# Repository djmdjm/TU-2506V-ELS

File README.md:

# Electronic Leadscrew for Optimum TU-2506V

This is a project to build an Electronic Leadscrew (ELS) for my bench
lathe, an Optimum TU-2506V. There are other lathes on the market that
seem to be based on the same casting (e.g. the Weiss WBL250F) that
might be compatible.

The project contains CAD designs for the mechanical parts, schematics,
PCB designs and firmware for the control board. More build photos
[here](https://photos.google.com/share/AF1QipOmF3oVsJtj0tLDA7D8ZUFRA7_QTG3Cf1XSVP2GjohUuVMBAQHxomHKcaGD1ETOJg?key=TW1sOVEwWHhqX3FoNWtXSDA4Q3BxZG1Bc1JGLTBn).

## Caveat

This works fine for me, but I'm just some guy on the internet with
little or no mechanical, electronic or software engineering training. 
There is no warranty for any of this, no guarantee that it will work,
no guarantee that it won't destroy your lathe, no promise that the
software won't crash in the middle of a job and scrap your part, etc.

Many of the mechanical pieces were manually made and even the
ones I CNC'd or had fabricated received some modifications that
aren't reflected in the CAD files. If you want to use this as the
basis of your own ELS, then be prepared to do some modifications of
your own.

## What you'll need (software)

The mechanical CAD designs were done in
[FreeCAD](https://www.freecad.org/) 0.21. For the parts that I CNC'd
myself, I also used FreeCAD's CAM processor to generate the G-Code.

The control boards was designed in [KiCAD](https://www.kicad.org/)
version 8 and were fabricated at JLCPCB. The PCB files have LCSC
annotations for automated assembly of the (few) SMT components.

The firmware for the control board was written in Rust using the
[stm32f4xx_hal](https://github.com/stm32-rs/stm32f4xx-hal) package.
I used rustc 1.81.0, but other versions might work too.

## What you'll need (hardware)

This lists only the main components. There are many small parts that
should be obvious from the CAD files, not to mention custom parts that
you'll need to make yourself or have fabricated.

The controller was designed around a
[STM32F411 "black pill"](https://www.dfrobot.com/product-2338.html) board.
These are also easily and cheaply available from hobbyist electronics
suppliers and from Ebay/Aliexpress.

The display is a
[Newhaven M0216SD‐162SDAR2-1](https://au.mouser.com/ProductDetail/Newhaven-Display/M0216SD-162SDAR2-1?qs=3vk7fz9CmNxwBN2LYkSmDA%3D%3D)
vacuum fluorescent display that I ordered from Mouser - this is a
fairly expensive part, but I love the aesthetics of a VFD.

The rest of the BOM for the controller can be extracted from the
KiCAD files for each of the respective boards. I mostly used parts that
I had on hand, so there are some odd choices in places.

The controller needs a 24VDC power supply at about 250mA in addition to
whatever the servo control needs. I used a Meanwell DIN rail mount PSU.

The servo motor I used a
[Teknic Clearpath CPM-SDSK-2331S-ELS](https://teknic.com/model-info/CPM-SDSK-2331S-ELS/).
Again, this is a fairly expensive choice and a cheaper stepper
motor + controller would probably do fine. The Clearpath drive does
have some very nice advantages over plain steppers or even cheap
closed-loop stepper drives. Whatever drive you choose, it obviously
needs to fit (NEMA 23 was close to the limit on my lathe) and you'll
need to provide a suitable power supply for it.

The spindle encoder I used was an
[Omron E6B2-CWZ1X](https://www.ia.omron.com/product/item/2382/). These are
ridiculously expensive if you buy them from anywhere reputable, but very
cheap on Ebay or Aliexpress.

The timing pulleys and belt used to connect the servo to the
leadscrew are standard HTD 5M parts. I got mine from PT Parts
([pulleys](https://www.ptparts.com.au/products/category/ALL/-12-5M-15--5m-15-htd-timing-pulleys):
20-5M-15F 40-5M-15F,
[belt](https://www.ptparts.com.au/products/category/ALL/-225-5M-15--5m-15-timing-belts): 350-5M-15),
but they should be fairly standard.

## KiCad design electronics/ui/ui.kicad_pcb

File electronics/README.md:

# Controller schematics and PCB designs

This directory contains the schematics and PCB CAD files for the controller
boards. To fit in the available space in the lathe casting they are designed
as a stack.

The `mcu/` subdirectory contains the designs for the MCU carrier board, which
basically exists to route signals from the STM32F411 Black Pill board to the
adjacent ones via headers. The character VFD display also connects to this
board via extended headers.

The `pwr_io/` subdirectory has the design for the isolated power and I/O board.
It has a couple of modular DC-DC converters that provide an isolated supply
to the MCU and display, and a separate isolated supply for the spindle encoder
and servo control lines.

The `ui/` subdirectory has the design for the carrier board for the rotary
encoders used on the front panel (you'll need two of these). These connect
via cables terminated in IDC connectors on the MCU board.

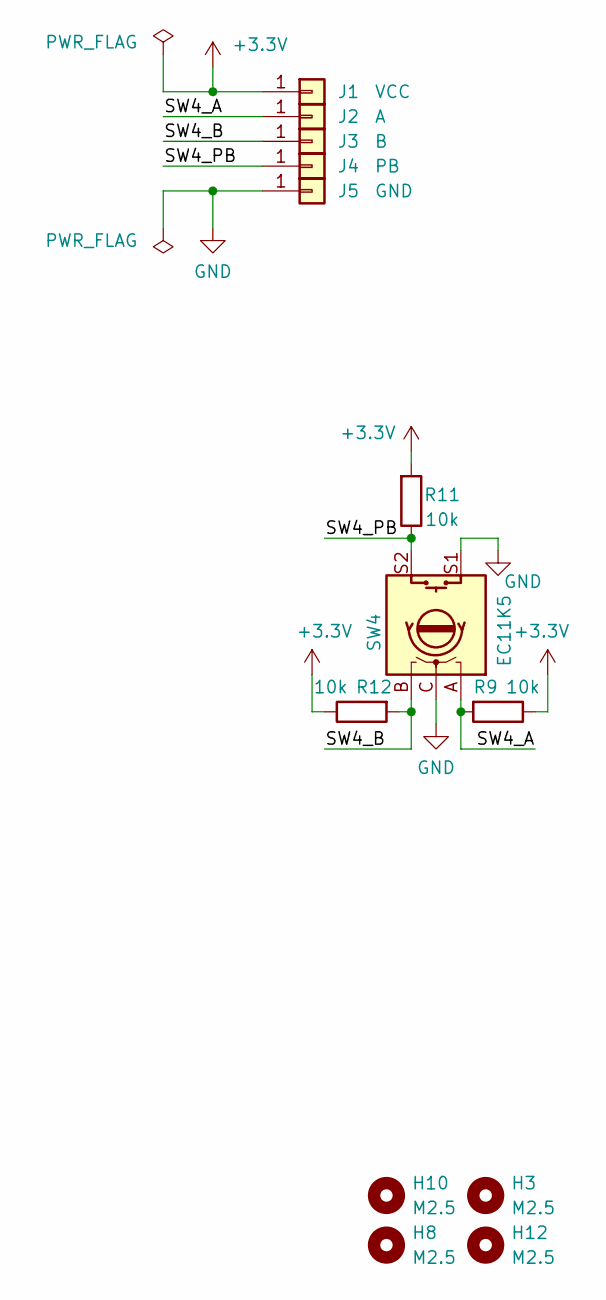
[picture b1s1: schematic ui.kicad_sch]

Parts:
H3, H8, H10, H12: M2.5; MountingHole_2.2mm_M2
J1: VCC; TestPoint_THTPad_D1.0mm_Drill0.5mm
J2: A; TestPoint_THTPad_D1.0mm_Drill0.5mm
J3: B; TestPoint_THTPad_D1.0mm_Drill0.5mm
J4: PB; TestPoint_THTPad_D1.0mm_Drill0.5mm
J5: GND; TestPoint_THTPad_D1.0mm_Drill0.5mm
R9, R11, R12: 10k; R_0805_2012Metric; LCSC C17414
SW4: EC11K5; EC11K15

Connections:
+3.3V: J1.1, R9.1, R11.2, R12.1
/SW4_A: J2.1, R9.2, SW4.A
/SW4_B: J3.1, R12.2, SW4.B
/SW4_PB: J4.1, R11.1, SW4.S2
GND: J5.1, SW4.C, SW4.S1

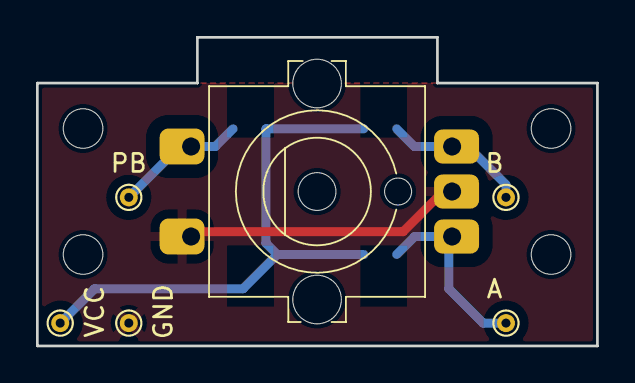
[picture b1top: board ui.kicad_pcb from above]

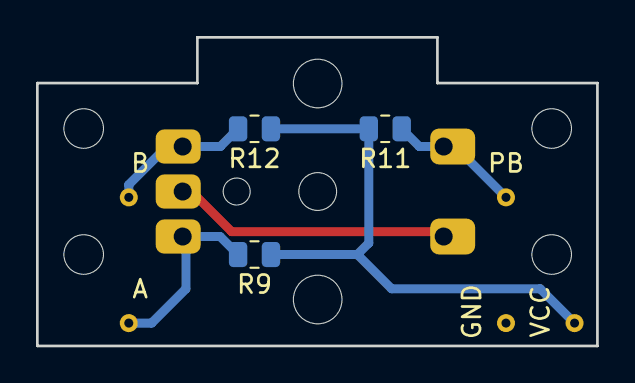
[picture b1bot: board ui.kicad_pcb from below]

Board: 2 copper layers, 31.1 x 17.1 mm, 13 parts (3 on the bottom side), 5 nets.

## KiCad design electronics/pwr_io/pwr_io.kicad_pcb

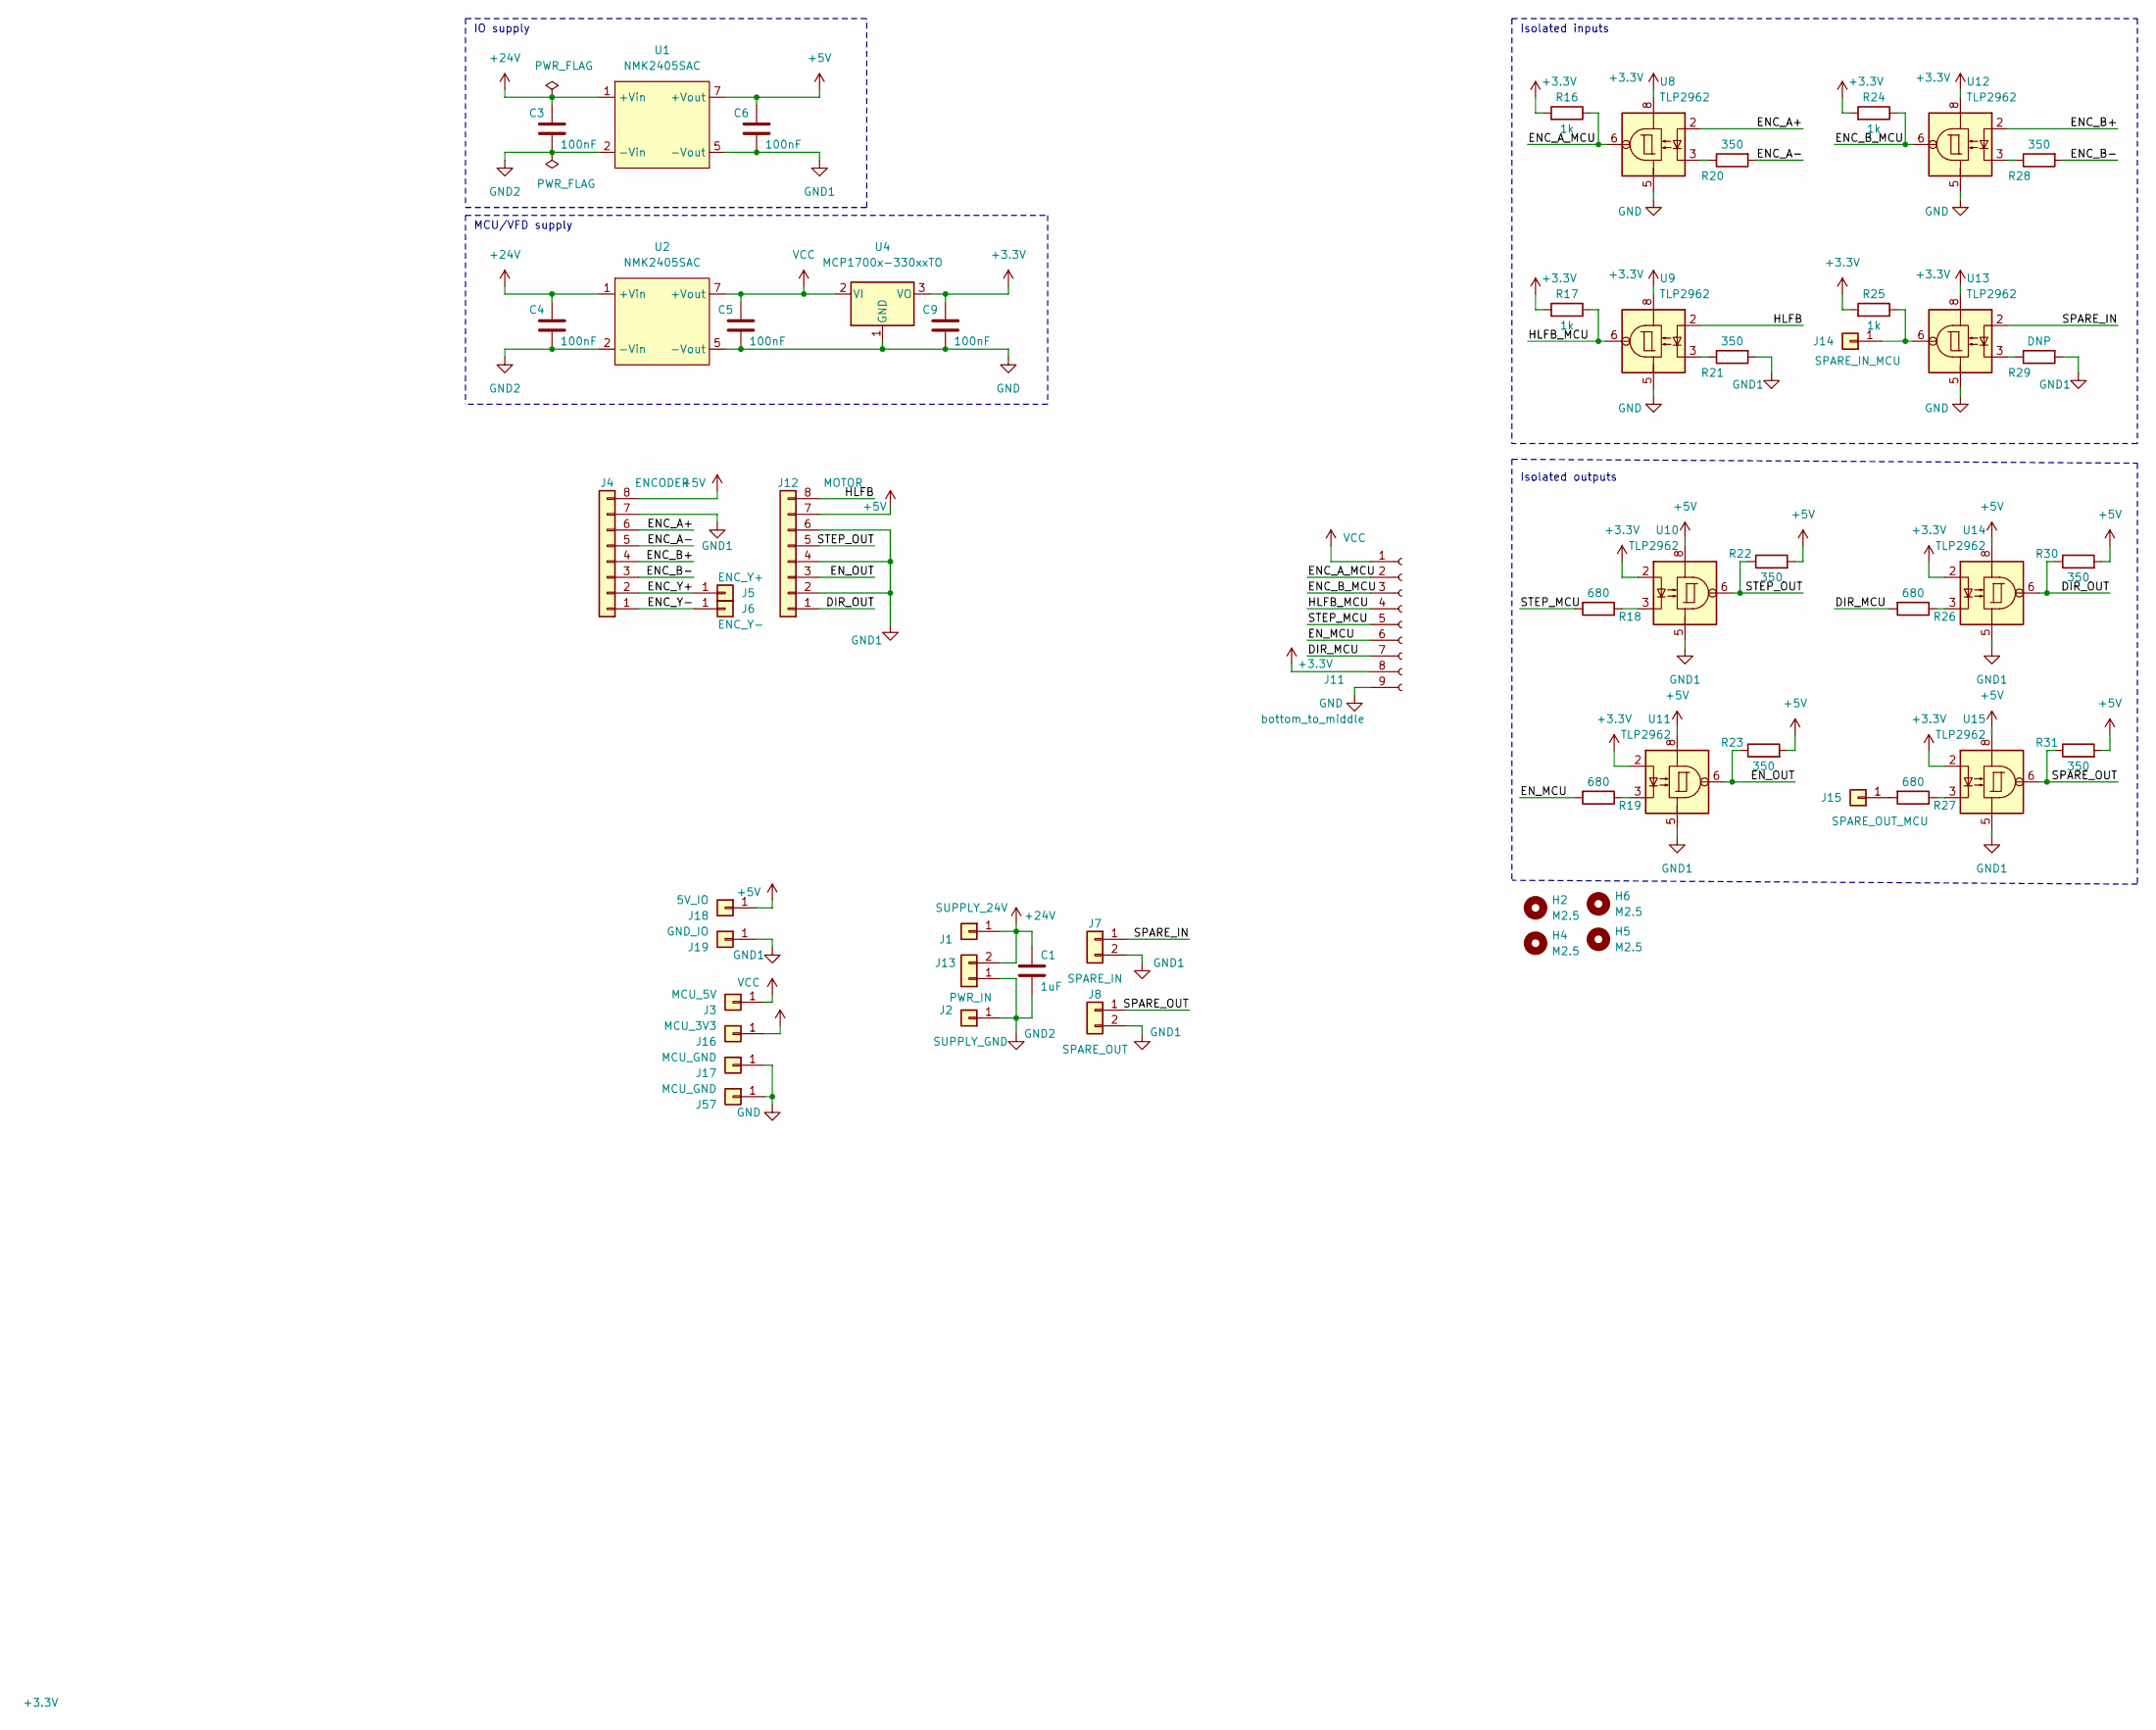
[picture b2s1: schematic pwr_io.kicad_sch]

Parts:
C1: 1uF; C_0805_2012Metric; LCSC C28323
C3, C4, C5, C6, C9: 100nF; C_0805_2012Metric; LCSC C28233
H2, H4, H5, H6: M2.5; MountingHole_2.7mm_M2.5
J1: SUPPLY_24V; TestPoint_THTPad_D1.5mm_Drill0.7mm
J2: SUPPLY_GND; TestPoint_THTPad_D1.5mm_Drill0.7mm
J3: MCU_5V; TestPoint_THTPad_D1.5mm_Drill0.7mm
J4: ENCODER; TerminalBlock_Phoenix_MKDS-1,5-8_1x08_P5.00mm_Horizontal
J5: ENC_Y+; TestPoint_THTPad_D1.5mm_Drill0.7mm
J6: ENC_Y-; TestPoint_THTPad_D1.5mm_Drill0.7mm
J7: SPARE_IN; TerminalBlock_Phoenix_MKDS-1,5-2_1x02_P5.00mm_Horizontal
J8: SPARE_OUT; TerminalBlock_Phoenix_MKDS-1,5-2_1x02_P5.00mm_Horizontal
J11: bottom_to_middle; PinHeader_1x09_P2.54mm_Vertical
J12: MOTOR; TerminalBlock_Phoenix_MKDS-1,5-8_1x08_P5.00mm_Horizontal
J13: PWR_IN; TerminalBlock_Phoenix_MKDS-1,5-2_1x02_P5.00mm_Horizontal
J14: SPARE_IN_MCU; TestPoint_THTPad_D1.5mm_Drill0.7mm
J15: SPARE_OUT_MCU; TestPoint_THTPad_D1.5mm_Drill0.7mm
J16: MCU_3V3; TestPoint_THTPad_D1.5mm_Drill0.7mm
J17, J57: MCU_GND; TestPoint_THTPad_D1.5mm_Drill0.7mm
J18: 5V_IO; TestPoint_THTPad_D1.5mm_Drill0.7mm
J19: GND_IO; TestPoint_THTPad_D1.5mm_Drill0.7mm
R16, R17, R24, R25: 1k; R_0805_2012Metric; LCSC C17513
R18, R19, R26, R27: 680; R_0805_2012Metric; LCSC C93658
R20, R21, R22, R23, R28, R30, R31: 350; R_0805_2012Metric; LCSC C245312
R29: DNP; R_0805_2012Metric
U1, U2: NMK2405SAC; NMK_single_output
U4: MCP1700x-330xxTO; TO-92_Inline
U8, U9, U10, U11, U12, U13, U14, U15: TLP2962; DIP-8_W7.62mm

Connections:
+3.3V: C9.1, J11.8, J16.1, R16.2, R17.2, R24.2, R25.2, U4.3 (VO), U8.8, U9.8, U10.2, U11.2, U12.8, U13.8, U14.2, U15.2
+5V: C6.1, J4.8, J12.7, J18.1, R22.2, R23.2, R30.2, R31.2, U1.7 (+Vout), U10.8, U11.8, U14.8, U15.8
+24V: C1.1, C3.1, C4.1, J1.1, J13.2, U1.1 (+Vin), U2.1 (+Vin)
/DIR_MCU: J11.7, R26.2
/DIR_OUT: J12.1, R30.1, U14.6
/ENC_A+: J4.6, U8.2
/ENC_A-: J4.5, R20.2
/ENC_A_MCU: J11.2, R16.1, U8.6
/ENC_B+: J4.4, U12.2
/ENC_B-: J4.3, R28.2
/ENC_B_MCU: J11.3, R24.1, U12.6
/ENC_Y+: J4.2, J5.1
/ENC_Y-: J4.1, J6.1
/EN_MCU: J11.6, R19.2
/EN_OUT: J12.3, R23.1, U11.6
/HLFB: J12.8, U9.2
/HLFB_MCU: J11.4, R17.1, U9.6
/SPARE_IN: J7.1, U13.2
/SPARE_OUT: J8.1, R31.1, U15.6
/STEP_MCU: J11.5, R18.2
/STEP_OUT: J12.5, R22.1, U10.6
GND: C5.2, C9.2, J11.9, J17.1, J57.1, U2.5 (-Vout), U4.1 (GND), U8.5, U9.5, U12.5, U13.5
GND1: C6.2, J4.7, J7.2, J8.2, J12.2, J12.4, J12.6, J19.1, R21.2, R29.2, U1.5 (-Vout), U10.5, U11.5, U14.5, U15.5
GND2: C1.2, C3.2, C4.2, J2.1, J13.1, U1.2 (-Vin), U2.2 (-Vin)
unnamed: J14.1, R25.1, U13.6
unnamed: J15.1, R27.2
unnamed: R18.1, U10.3
unnamed: R19.1, U11.3
unnamed: R20.1, U8.3
unnamed: R21.1, U9.3
unnamed: R26.1, U14.3
unnamed: R27.1, U15.3
unnamed: R28.1, U12.3
unnamed: R29.1, U13.3
VCC: C5.1, J3.1, J11.1, U2.7 (+Vout), U4.2 (VI)

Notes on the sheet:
Isolated outputs
Isolated inputs
IO supply
MCU/VFD supply

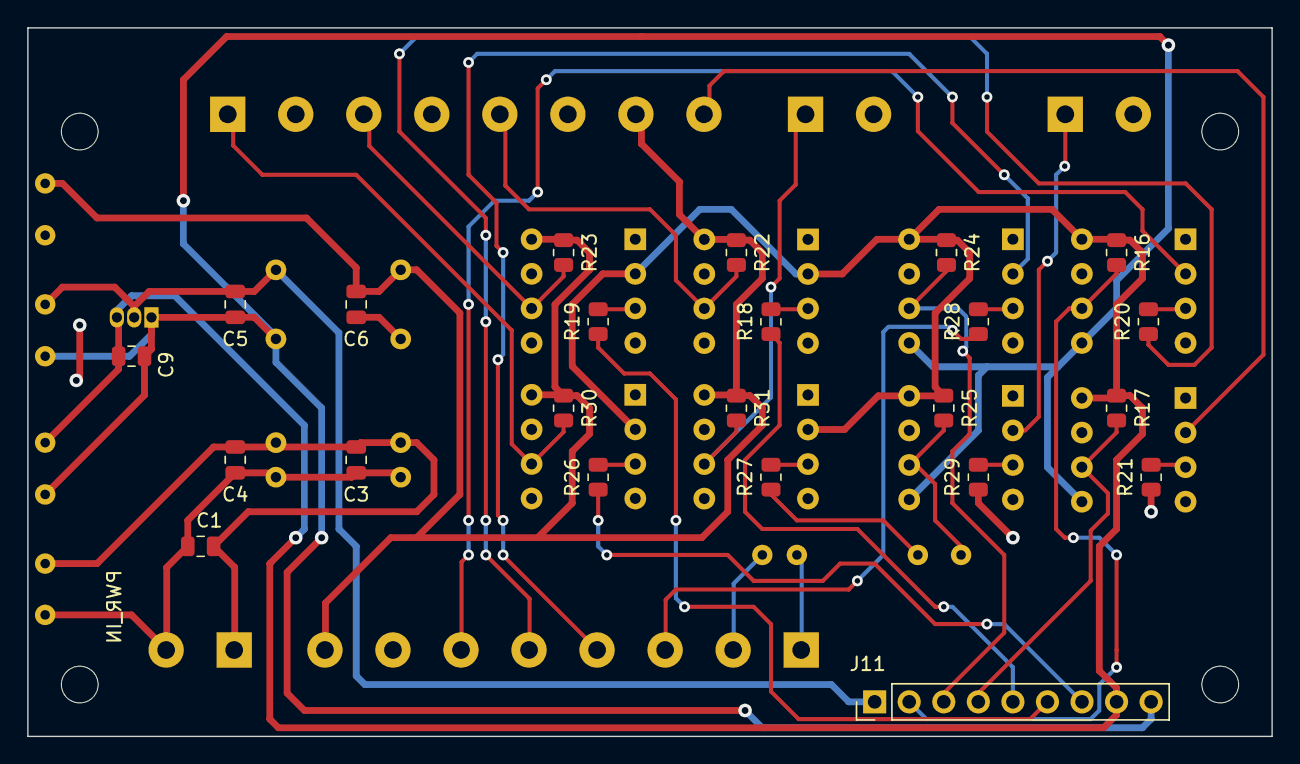
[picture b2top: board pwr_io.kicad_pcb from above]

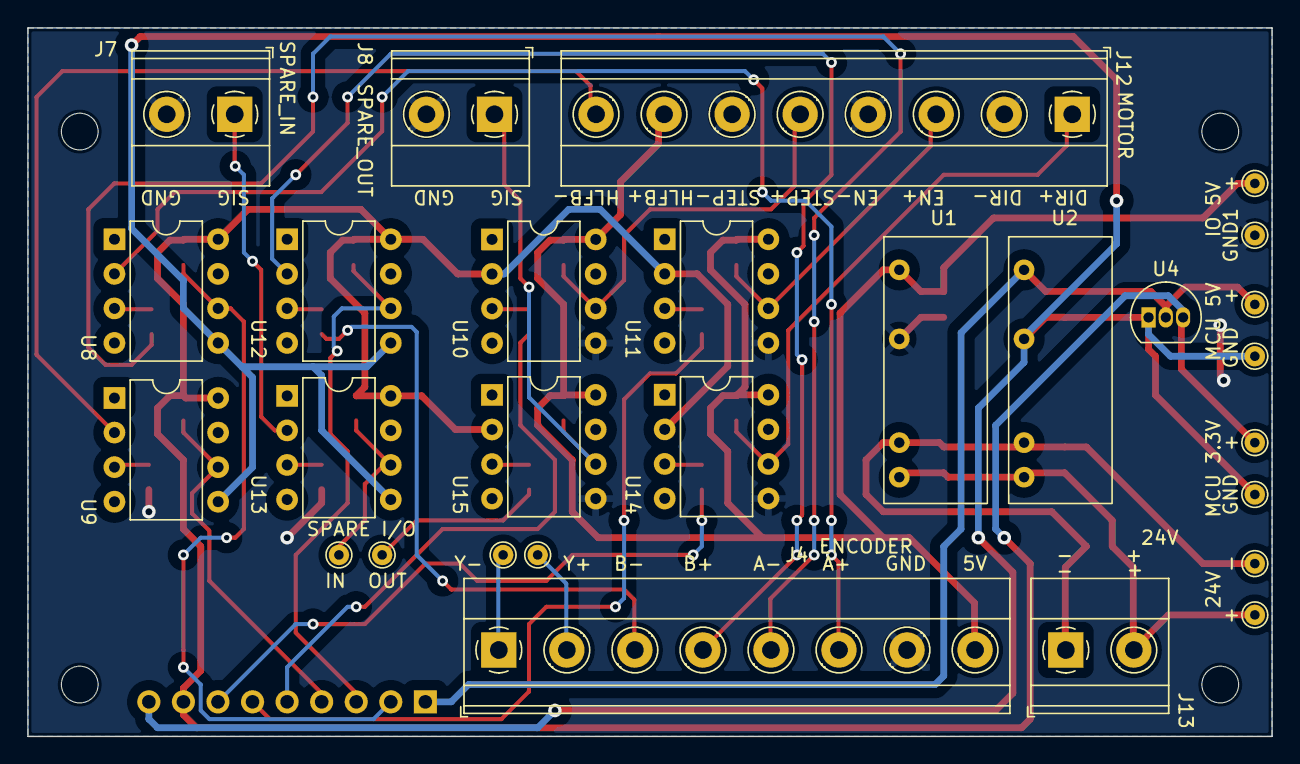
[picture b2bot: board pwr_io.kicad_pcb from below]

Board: 2 copper layers, 91.4 x 52.1 mm, 55 parts (28 on the bottom side), 35 nets.

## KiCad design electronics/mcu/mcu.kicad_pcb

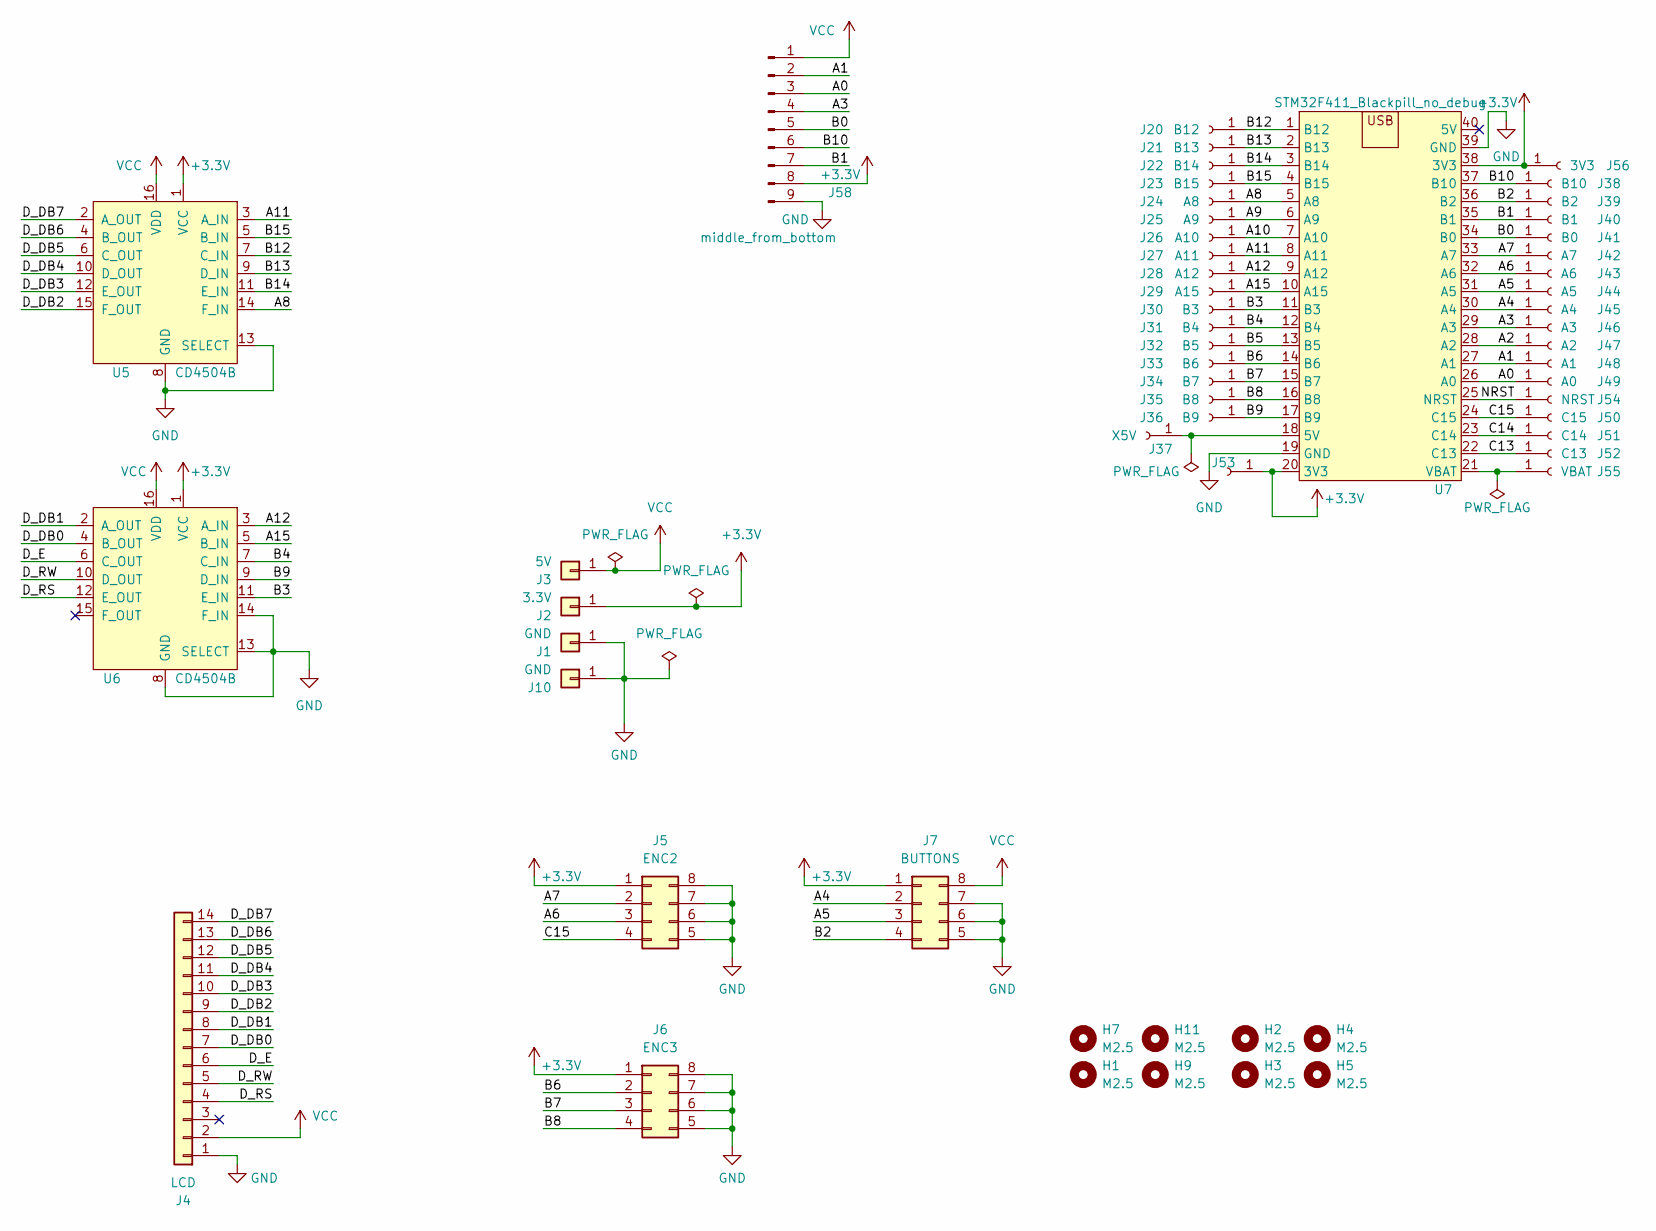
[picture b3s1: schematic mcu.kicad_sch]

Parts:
H1, H2, H3, H4, H5, H7, H9, H11: M2.5; MountingHole_2.7mm_M2.5
J1, J10: GND; TestPoint_THTPad_D1.5mm_Drill0.7mm
J2: 3.3V; TestPoint_THTPad_D1.5mm_Drill0.7mm
J3: 5V; TestPoint_THTPad_D1.5mm_Drill0.7mm
J4: LCD; PinHeader_1x14_P2.54mm_Vertical
J5: ENC2; IDC-Header_2x04_P2.54mm_Vertical
J6: ENC3; IDC-Header_2x04_P2.54mm_Vertical
J7: BUTTONS; IDC-Header_2x04_P2.54mm_Vertical
J20: B12; TestPoint_THTPad_D1.5mm_Drill0.7mm
J21: B13; TestPoint_THTPad_D1.5mm_Drill0.7mm
J22: B14; TestPoint_THTPad_D1.5mm_Drill0.7mm
J23: B15; TestPoint_THTPad_D1.5mm_Drill0.7mm
J24: A8; TestPoint_THTPad_D1.5mm_Drill0.7mm
J25: A9; TestPoint_THTPad_D1.5mm_Drill0.7mm
J26: A10; TestPoint_THTPad_D1.5mm_Drill0.7mm
J27: A11; TestPoint_THTPad_D1.5mm_Drill0.7mm
J28: A12; TestPoint_THTPad_D1.5mm_Drill0.7mm
J29: A15; TestPoint_THTPad_D1.5mm_Drill0.7mm
J30: B3; TestPoint_THTPad_D1.5mm_Drill0.7mm
J31: B4; TestPoint_THTPad_D1.5mm_Drill0.7mm
J32: B5; TestPoint_THTPad_D1.5mm_Drill0.7mm
J33: B6; TestPoint_THTPad_D1.5mm_Drill0.7mm
J34: B7; TestPoint_THTPad_D1.5mm_Drill0.7mm
J35: B8; TestPoint_THTPad_D1.5mm_Drill0.7mm
J36: B9; TestPoint_THTPad_D1.5mm_Drill0.7mm
J37: X5V; TestPoint_THTPad_D1.5mm_Drill0.7mm
J38: B10; TestPoint_THTPad_D1.5mm_Drill0.7mm
J39: B2; TestPoint_THTPad_D1.5mm_Drill0.7mm
J40: B1; TestPoint_THTPad_D1.5mm_Drill0.7mm
J41: B0; TestPoint_THTPad_D1.5mm_Drill0.7mm
J42: A7; TestPoint_THTPad_D1.5mm_Drill0.7mm
J43: A6; TestPoint_THTPad_D1.5mm_Drill0.7mm
J44: A5; TestPoint_THTPad_D1.5mm_Drill0.7mm
J45: A4; TestPoint_THTPad_D1.5mm_Drill0.7mm
J46: A3; TestPoint_THTPad_D1.5mm_Drill0.7mm
J47: A2; TestPoint_THTPad_D1.5mm_Drill0.7mm
J48: A1; TestPoint_THTPad_D1.5mm_Drill0.7mm
J49: A0; TestPoint_THTPad_D1.5mm_Drill0.7mm
J50: C15; TestPoint_THTPad_D1.5mm_Drill0.7mm
J51: C14; TestPoint_THTPad_D1.5mm_Drill0.7mm
J52: C13; TestPoint_THTPad_D1.5mm_Drill0.7mm
J53, J56: 3V3; TestPoint_THTPad_D1.5mm_Drill0.7mm
J54: NRST; TestPoint_THTPad_D1.5mm_Drill0.7mm
J55: VBAT; TestPoint_THTPad_D1.5mm_Drill0.7mm
J58: middle_from_bottom; PinSocket_1x09_P2.54mm_Vertical
U5, U6: CD4504B; DIP-16_W7.62mm
U7: STM32F411_Blackpill_no_debug; BlackPill_V3_no_debug

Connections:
+3.3V: J2.1, J5.1, J6.1, J7.1, J53.1, J56.1, J58.8, U5.1 (VCC), U6.1 (VCC), U7.20 (3V3), U7.38 (3V3)
/A0: J49.1, J58.3, U7.26 (A0)
/A1: J48.1, J58.2, U7.27 (A1)
/A2: J47.1, U7.28 (A2)
/A3: J46.1, J58.4, U7.29 (A3)
/A4: J7.2, J45.1, U7.30 (A4)
/A5: J7.3, J44.1, U7.31 (A5)
/A6: J5.3, J43.1, U7.32 (A6)
/A7: J5.2, J42.1, U7.33 (A7)
/A8: J24.1, U5.14 (F_IN), U7.5 (A8)
/A9: J25.1, U7.6 (A9)
/A10: J26.1, U7.7 (A10)
/A11: J27.1, U5.3 (A_IN), U7.8 (A11)
/A12: J28.1, U6.3 (A_IN), U7.9 (A12)
/A15: J29.1, U6.5 (B_IN), U7.10 (A15)
/B0: J41.1, J58.5, U7.34 (B0)
/B1: J40.1, J58.7, U7.35 (B1)
/B2: J7.4, J39.1, U7.36 (B2)
/B3: J30.1, U6.11 (E_IN), U7.11 (B3)
/B4: J31.1, U6.7 (C_IN), U7.12 (B4)
/B5: J32.1, U7.13 (B5)
/B6: J6.2, J33.1, U7.14 (B6)
/B7: J6.3, J34.1, U7.15 (B7)
/B8: J6.4, J35.1, U7.16 (B8)
/B9: J36.1, U6.9 (D_IN), U7.17 (B9)
/B10: J38.1, J58.6, U7.37 (B10)
/B12: J20.1, U5.7 (C_IN), U7.1 (B12)
/B13: J21.1, U5.9 (D_IN), U7.2 (B13)
/B14: J22.1, U5.11 (E_IN), U7.3 (B14)
/B15: J23.1, U5.5 (B_IN), U7.4 (B15)
/C13: J52.1, U7.22 (C13)
/C14: J51.1, U7.23 (C14)
/C15: J5.4, J50.1, U7.24 (C15)
/D_DB0: J4.7, U6.4 (B_OUT)
/D_DB1: J4.8, U6.2 (A_OUT)
/D_DB2: J4.9, U5.15 (F_OUT)
/D_DB3: J4.10, U5.12 (E_OUT)
/D_DB4: J4.11, U5.10 (D_OUT)
/D_DB5: J4.12, U5.6 (C_OUT)
/D_DB6: J4.13, U5.4 (B_OUT)
/D_DB7: J4.14, U5.2 (A_OUT)
/D_E: J4.6, U6.6 (C_OUT)
/D_RS: J4.4, U6.12 (E_OUT)
/D_RW: J4.5, U6.10 (D_OUT)
/NRST: J54.1, U7.25 (NRST)
GND: J1.1, J4.1, J5.5, J5.6, J5.7, J5.8, J6.5, J6.6, J6.7, J6.8, J7.5, J7.6, J7.7, J10.1, J58.9, U5.8 (GND), U5.13 (SELECT), U6.8 (GND), U6.13 (SELECT), U6.14 (F_IN), U7.19 (GND), U7.39 (GND)
unnamed: J37.1, U7.18 (5V)
unnamed: J55.1, U7.21 (VBAT)
VCC: J3.1, J4.2, J7.8, J58.1, U5.16 (VDD), U6.16 (VDD)

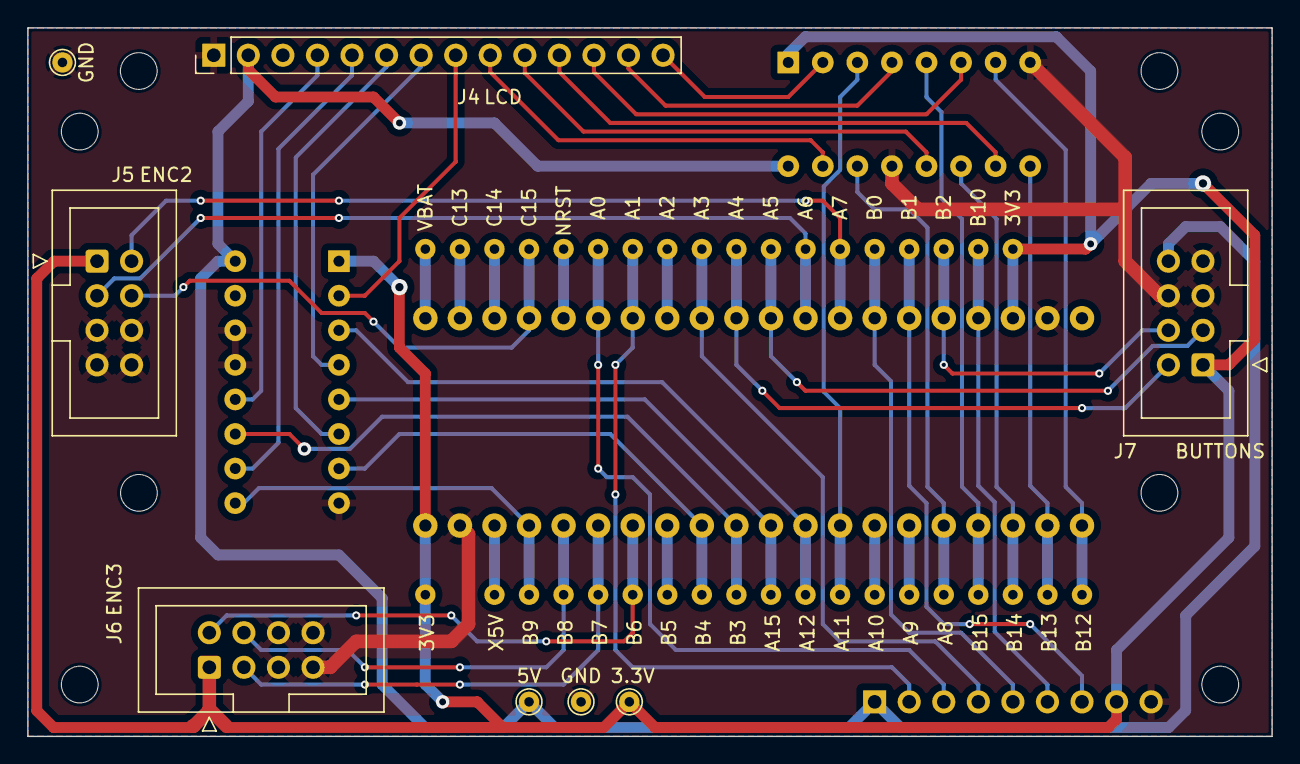
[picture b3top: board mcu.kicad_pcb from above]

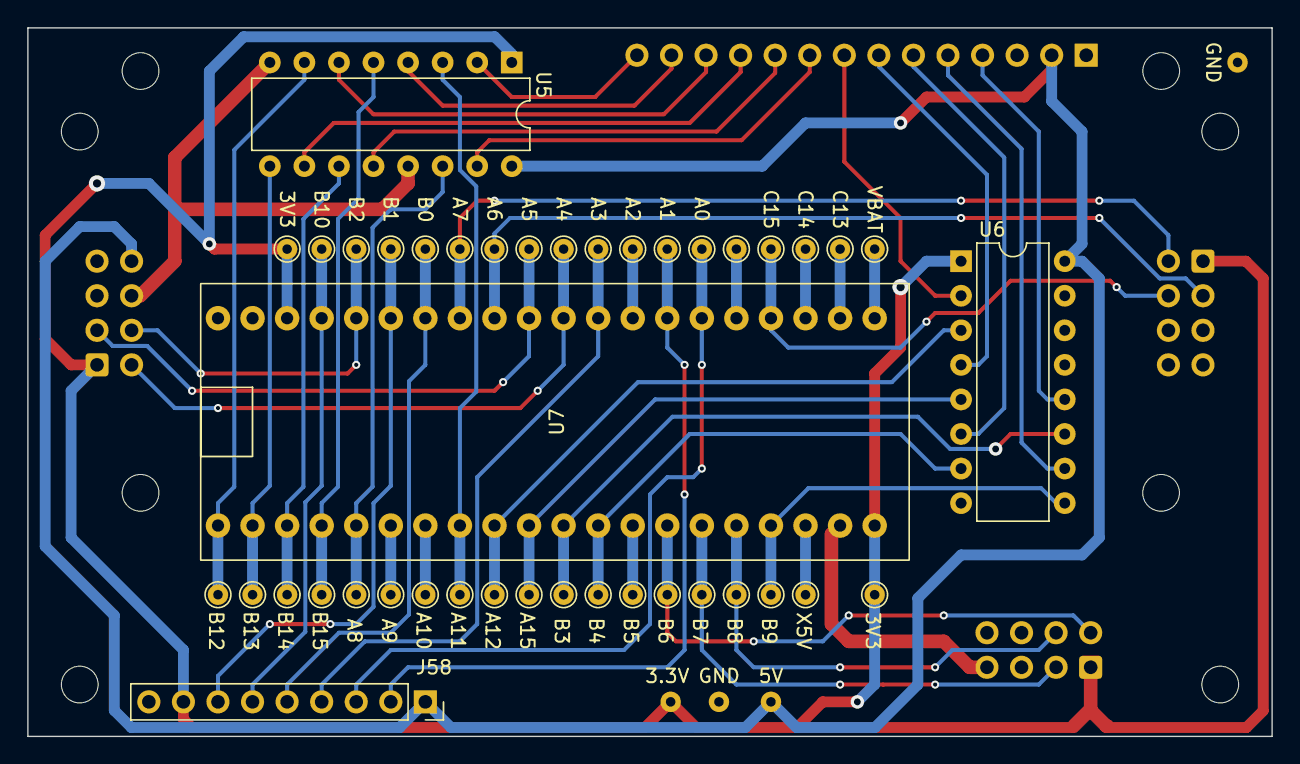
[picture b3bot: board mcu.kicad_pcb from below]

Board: 2 copper layers, 91.4 x 52.1 mm, 57 parts (41 on the bottom side), 49 nets.

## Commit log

2024-09-27 import
2024-09-27 readme to electronics
2024-09-27 license
2024-09-27 more documentation
2024-09-27 TODO
2024-09-27 more detail
2024-09-27 wrong directory
2024-09-27 picture
2024-09-27 link to build photos
2024-09-27 fix link
2024-09-27 tweak readme
2024-09-27 tweak readmes
2024-10-09 improve TPI threading mode
    Use full range of 32.32 fixed point math for TPI feed rate rather
    than microns/rev approximation.
2024-10-11 better TPI mode is done, mention other caveats
2024-11-17 bugfix: reentering Servo Off didn't disable servo
2024-11-17 bug: Servo Off incorrectly displayed servo error
2024-11-17 ui tweaks for safety
    Require the mode encoder button to be depressed to change mode.
    Likewise, require the feed button to be depressed to change thread
    pitch.
    Found out the hard way that it's fairly easy to bump a control knob
    during a threading operation.
    Move debug mode to requiring both mode+feed encoder buttons be held
2024-11-29 remove stale comment
